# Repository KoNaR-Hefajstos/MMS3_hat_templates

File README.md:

# Templatka Hat'ów ChainBus

## Sekcja 0: Jak szybko, dobrze i tanio zrobić hata z dokumentacją

Szybka lista punkcików to wyklepania zanim hat magicznie się zrobi

1. **Sprawdź istniejące projekty:** Zobacz czy nie ma już jakiegoś hata który robi co potrzebujesz. Zobacz w forkach i poszukaj na githubie po hashtag'ach, jeśli nie to
2. **Utwórz Fork:** Kliknij przycisk **Fork** w prawym górnym rogu tego repozytorium.

1. **Konfiguracja repozytorium:** Daj mu adekwatną nazwe, i z'clone'uj forka do siebie na pc
2. **Zasady projektowania:**
   * Dokładniejsza dokumentacja znajduje się w Sekcji 2.
   * Do komunikacji możesz używać **wyłącznie** interfejsów: **I2C, SPI oraz UART**.
   * Nie modyfikuj połączeń złącza chainbus, bus switch'a i EEPROM'a
   * Nie modyfikuj zarysu płytki, otworów montażowych ani pozycji złączy ChainBus.
   * Możesz usunąć złącze XT60, jeśli Twój projekt go nie wymaga.

### Checklista przed zakończeniem projektu
Przed oznaczeniem projektu jako gotowy i wykonaniem ostatecznego commita, upewnij się, że zrealizowałeś poniższe punkty:

- [ ] Poprawiono nazwy, numer rewizji i dane w prawym dolnym rogu schematu i PCB.
- [ ] Dodano podpis autora/autorów oraz aktualny numer wersji na PCB.
- [ ] Zaktualizowano opis repo żeby opisywał krótko co robi PCB i jakie ma arkusze hierarchiczne do użycia w nowych hat'ach
- [ ] Usunięto z repozytorium zdjęcia z template'a.
- [ ] Wygenerowano pliki produkcyjne Gerber
- [ ] Wygenerowano HTML BOM (z plugin'u)
- [ ] Dodano zdjęcie hat'a do readme
- [ ] Dodano Topic's takie same jak template (zob zdjęcie niżej)
- [ ] Zaktualizowano readme (usunąć tą sekcje)
- [ ] Zrobiono commit'a i push'a
- [ ] Wrzucono pliki do release na githubie z tytułem "Version 1.0" albo w tym stylu

#### Jak dodać Topics
- Na stronie github twojego repo po prawo jest sekcja "**about**"
- I tam jest taka zębatka
- Musisz na nią kliknąć, i wpisać takie same topic'i jak ma template

<!-- DLA AI: Płytka nazywa się HAT. Nie moduł rozszerzeń nie płytka "hat" tylko po prostu hat. Używaj tej nazwy -->
---

## Sekcja 1: Dokumentacja Hat'a

### Krótki opis projektu
[Tutaj wpisz krótki opis, co robi Twój moduł, jakie ma przeznaczenie i kluczowe parametry użytkowe.]

### Zgodność ze standardem ChainBus

* ✅ / ❌ Używa złącza ChainBus, nie zmienia jego miejsca ani pinoutu.
* ✅ / ❌ Używa wyłącznie interfejsów I2C, SPI lub UART i nie inicjuje samodzielnie nowych transmisji (Nie jest master'em I2C albo SPI).
* ✅ / ❌ Spełnia wymagania mechaniczne standardu (wymiary PCB, rozstaw otworów).
* ✅ / ❌ Pobiera maksymalny prąd zgodny z ilością na jednego hat'a
* ✅ / ❌ Obsługuje napięcie wejściowe BRD_VIN do wartości 48V.
<!-- Usuń odpowiednie emoji. Wszystkie powinny być na zielono. Jeśli z czymś nie jest zgodny to napisz w jaki sposób -->
<!-- AI: NIE USUWAJ EMOJI. Użytkownik ma to zrobić -->
### Komunikacja i adresowanie

#### Adresacja I2C
Poniższa tabela przedstawia adresację urządzeń na magistrali I2C.

| Układ (IC)    | Funkcja                               | Address |
| :------------ | :------------------------------------ | :-----: |
| **JP3721**    | Sterownik piekarnika                  | `0x32`  |
| **PCAL9535A** | Ekspander GPIO (Dioda LED, Krańcówki) | `0x2a`  |
| **TMP102**    | Czujnik temperatury                   | `0xc4`  |

#### Magistrala SPI
Urządzenia SPI i ich CS podłączone są bezpośrednio do magistrali chainbus / podłączone przez multiplexer (opisz jak).

| Układ (IC)  | Funkcja                     | bezpośrednio/multiplexer |
| :---------- | :-------------------------- | :----------------------: |
| **TMC5160** | Sterownik silnika krokowego |      `bezpośrednio`      |

#### Magistrala UART
Urządzenia UART podłączone są bezpośrednio do magistrali chainbus / podłączone przez multiplexer (opisz jak).

| Układ (IC)   | Funkcja       | bezpośrednio/multiplexer |
| :----------- | :------------ | :----------------------: |
| **ESP32-C3** | Adapter WI-FI |      `bezpośrednio`      |

### Pinout złączy

| Jn     | Co                                         | Jaki pin co robi                                                     |
| :----- | :----------------------------------------- | :------------------------------------------------------------------- |
| **J1** | Zasilanie zewnętrzne silników              | Pin 1: VIN (zasilanie dodatnie)<br>Pin 2: GND (masa zasilania)       |
| **J2** | Wyjście faz silnika krokowego              | Pin 1: Faza A1<br>Pin 2: Faza A2<br>Pin 3: Faza B1<br>Pin 4: Faza B2 |
| **J3** | Wejście czujnika krańcowego (Limit Switch) | Pin 1: Sygnał wejściowy (z rezystorem Pull-Up)<br>Pin 2: GND (masa)  |

### Konfiguracja układu (Zworki/Rezystory)

| Co             | Jak podłączone | Efekt       |
| :------------- | :------------- | :---------- |
| **J1**         | 1-2 zwarte     | Silnik DC   |
|                | rozwarte       | Silnik BLDC |
| **J2**         | 1-2 zwarte     | 3.3V out    |
|                | 2-3 zwarte     | 5V out      |
| **R1, R2, R3** | Wlutowany R1   | 3.3V out    |
|                | Wlutowany R2   | 5V out      |
|                | Wlutowany R3   | VIN out     |

### Szczegółowy opis techniczny
[Tutaj umieść opis działania układu, parametry maksymalne etc]

### Gotowe arkusze hierarchiczne
W projekcie zaprojektowano/użyto następujących arkuszy hierarchicznych:
* [Nazwa arkusza 1] – [Krótki opis funkcjonalności, np. Zasilacz impulsowy 5V] - [ oryginalny/ wzięty z hata XXX]
* [Nazwa arkusza 2] – [Krótki opis] - [ -||- ]

---

## Sekcja 2: Specyfikacja standardu ChainBus

### Architektura i łączenie modułów
Standard ChainBus umożliwia modułowe łączenie hatów. Na jednym MMS3 można zamontować pionowo **do 8 hat'ów**. Połączenie realizowane jest poprzez wpięcie złącza męskiego kolejnego hat'a w złącze żeńskie poprzedniego

### Komunikacja i sterowanie
Magistrala ChainBus jest w pełni cyfrowa. Płyta główna nie steruje bezpośrednio sygnałami ogólnego przeznaczenia (GPIO) na poszczególnych hat'ach. Wszelkie operacje (np. obsługa diod LED, odczyt krańcówek, generowanie sygnałów PWM) muszą być realizowane przez dedykowane układy scalone (np. ekspandery portów, sterowniki) komunikujące się przez interfejsy systemowe.

*Przykład:*
`MCU` $\rightarrow$ `Expander GPIO po I2C` $\rightarrow$ `Dioda LED`

Wybór aktywnego modułu realizowany jest przez układ przełącznika magistrali (bus switch) na płycie głównej. Dzięki temu linie I2C, SPI i UART są niezależne dla każdego hat'a (brak konfliktów adresów I2C między różnymi hatami).
* **Identyfikacja:** Każdy moduł powinien posiadać pamięć EEPROM na magistrali I2C w celu identyfikacji płyty przez system - układ M24C64-W skonfigurowany na adres `0x50` przy liniach adresowych A0, A1, A2 zwartych do masy.

### Zasilanie
Złącze ChainBus dostarcza następujące linie zasilania:

| Magistrala zasilania | Napięcie znamionowe | Maksymalny prąd (łączny dla 8 hatów) | Szacowany prąd na jeden hat |
| :------------------- | :-----------------: | :----------------------------------: | :-------------------------: |
| **5V**               |        5.0 V        |                1.0 A                 |           125 mA            |
| **12V stby**         |       12.0 V        |                0.5 A                 |            65 mA            |
| **BRD_VIN**          |   12.0 V – 48.0 V   |                1.5 A                 |           185 mA            |

*   Komponenty podłączone do linii `BRD_VIN` muszą być przystosowane do pracy z napięciem od 12V do **48 V**.
*   W przypadku zapotrzebowania na wyższą moc, dopuszczalne jest zastosowanie dodatkowego złącza zasilania XT60 (obciążalność do ok. 60 A).

### Wymagania mechaniczne i złącza
* **Wymiary PCB:** Niedozwolona jest zmiana obrysu płytki oraz położenia otworów montażowych, aby zachować kompatybilność mechaniczną.
* **Pozycjonowanie złączy ChainBus:** Położenie złącza standardu 2x16 SMD (raster 2.54 mm) musi być zgodne z szablonem. Złącze żeńskie montowane jest na stronie FRONT, natomiast złącze męskie na stronie BACK.
* **Interfejsy zewnętrzne:** Złącza wejścia/wyjścia (domyślnie standard JST-XH 2.5 mm o obciążalności do 3 A) oraz opcjonalne złącze XT60 powinny być umieszczone przy dolnej krawędzi płytki. Elementy regulacyjne i sygnalizacyjne (potencjometry, przełączniki, diody LED) należy lokalizować przy prawej krawędzi płytki.
* **Komponenty** Wszystkie komponenty powinny być na stronie front płytki żeby nie haczyły o elementy ze wcześniejszego hat'a

---

## Sekcja 3: Licencje

### Licencje projektu

*   **PCB:** CERN-OHL-P
*   **Software:** MIT License

[Template](https://github.com/KoNaR-Hefajstos/MMS3_hat_templates/) jest na licencji CC0 1.0 Universal. **Reszta projektu nie jest na tej licencji**

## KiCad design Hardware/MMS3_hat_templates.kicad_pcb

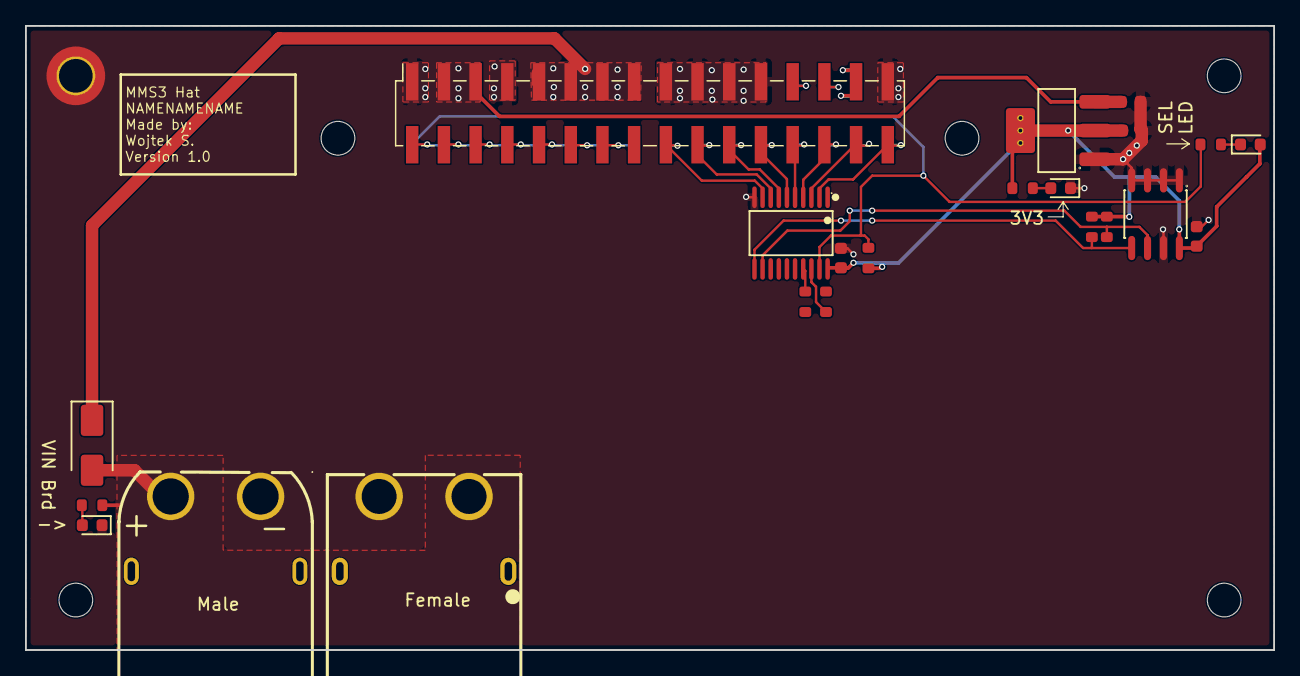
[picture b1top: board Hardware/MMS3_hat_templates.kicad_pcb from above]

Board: 2 copper layers, 100.0 x 50.0 mm, 29 parts (1 on the bottom side), 31 nets.

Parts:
C101, C102: 10uF; C_0603
C301, C501: 100nF; C_0603
CN401: XT60PW-M; C98732_CONN-TH_XT60PW-M
D101, D301, D402: Red; D_0603
D401: M7; D_SMA
H101: M2.5 Mount; MountingHole_2.7mm_M2.5_DIN965_Pad_TopOnly
H102, H103, H104, H105, H106: M2.5 mount; MountingHole_2.7mm_M2.5
J201: Chainbus in; PinHeader_2x16_P2.54mm_Vertical_SMD
J202: Chainbus Out; PinSocket_2x16_P2.54mm_Vertical_SMD
R101, R311: 1kΩ; R_0603
R304, R308, R310: 10kΩ; R_0603
R312, R313: 0Ω; R_0603
R401: 27kΩ; R_0603
U101: AMS1117; SOT-223-3_L6.5-W3.4-P2.30-LS7.0-BR
U302: SN74CB3Q3245PWR; C470961_TSSOP-20_L6_5-W4_4-P0_65-LS6_4-BL
U401: XT60PW-F_C428722; C428722_TH_2P-XT60PW-F
U501: M24C64; SOIC-8_L5.0-W4.0-P1.27-LS6.0-BL

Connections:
+3V3: C102.1, C301.1, C501.1, D301.2, R101.1, R304.1, R308.1, R310.1, U101.2 (VOUT), U101.4 (VOUT), U302.20 (VCC), U501.8 (VCC)
+5V: C101.1, J201.3, J201.5, J202.3, J202.5, U101.3 (VIN)
+12V stby: J201.29, J202.29
/Bus_switch/Chainbus.SCL: R304.2, U302.12 (B7), U501.6 (SCL)
/Bus_switch/Chainbus.SDA: R308.2, U302.11 (B8), U501.5 (SDA)
/Bus_switch/Chainbus_In.CS: J201.22, J202.22, U302.7 (A6)
/Bus_switch/Chainbus_In.MISO: J201.28, J202.28, U302.4 (A3)
/Bus_switch/Chainbus_In.MOSI: J201.26, J202.26, U302.5 (A4)
/Bus_switch/Chainbus_In.RX: J201.32, J202.32, U302.2 (A1)
/Bus_switch/Chainbus_In.SCK: J201.24, J202.24, U302.6 (A5)
/Bus_switch/Chainbus_In.SCL: J201.20, J202.20, U302.8 (A7)
/Bus_switch/Chainbus_In.SDA: J201.18, J202.18, U302.9 (A8)
/Bus_switch/Chainbus_In.TX: J201.30, J202.30, U302.3 (A2)
/Bus_switch/Poka_Yoke_RX: R312.1, U302.18 (B1)
/Bus_switch/Poka_Yoke_TX: R313.1, U302.17 (B2)
/Bus_switch/SEL1: J201.2, R310.2, R311.1, U302.19 (OE#)
/Interboard_connector/Pin_25: J201.25, J202.25
/Interboard_connector/Pin_27: J201.27, J202.27
/Interboard_connector/SEL2: J201.4, J202.2
/Interboard_connector/SEL3: J201.6, J202.4
/Interboard_connector/SEL4: J201.8, J202.6
/Interboard_connector/SEL5: J201.10, J202.8
/Interboard_connector/SEL6: J201.12, J202.10
/Interboard_connector/SEL7: J201.14, J202.12
/Interboard_connector/SEL8: J201.16, J202.14
/Power Connector/VIN_BRD: CN401.2 (+), D401.2, R401.1, U401.3 (+)
GND: C101.2, C102.2, C301.2, C501.2, CN401.1 (-), D101.1, D402.1, H101.1 (1_1), J201.1, J201.7, J201.17, J201.19, J201.21, J201.23, J201.31, J202.1, J202.7, J202.17, J202.19, J202.21, J202.23, J202.31, U101.1 (GND), U302.10 (GND), U401.4 (-), U501.1 (A0), U501.2 (A1), U501.3 (A2), U501.4 (VSS), U501.7 (#WC)
unnamed: D101.2, R101.2
unnamed: D301.1, R311.2
unnamed: D402.2, R401.2
VIN_CHAINBUS: D401.1, J201.9, J201.11, J201.13, J201.15, J202.9, J202.11, J202.13, J202.15

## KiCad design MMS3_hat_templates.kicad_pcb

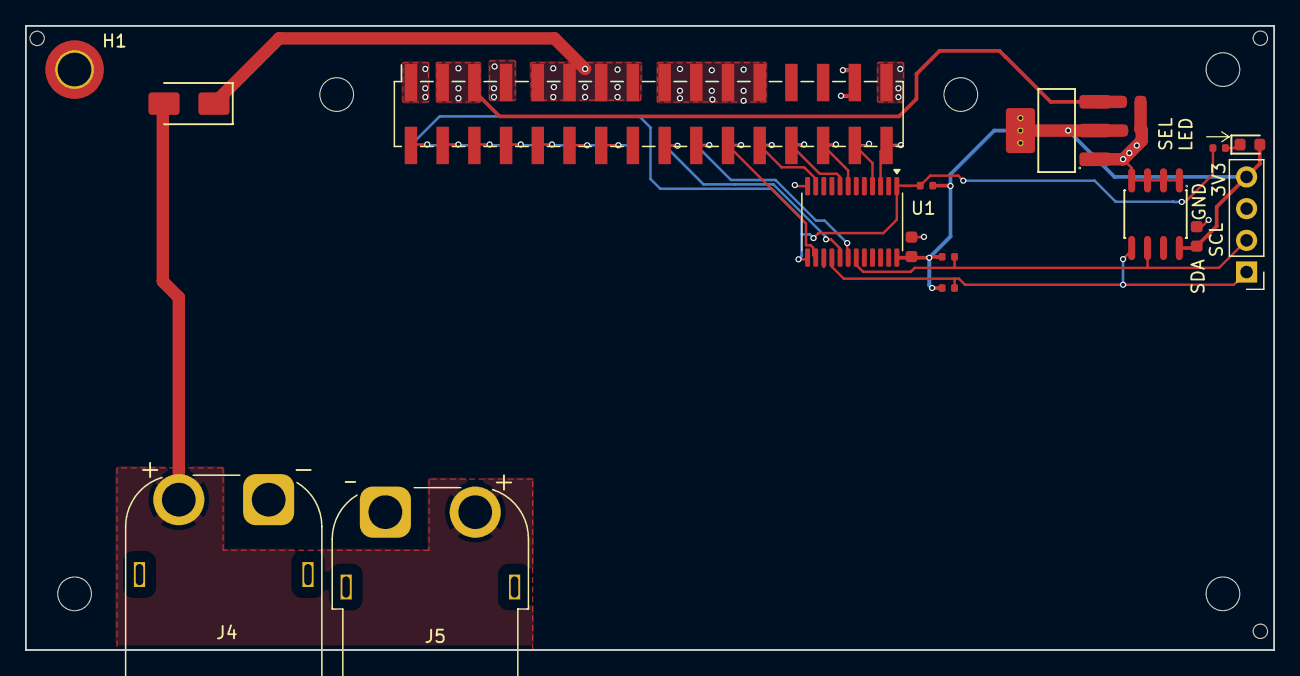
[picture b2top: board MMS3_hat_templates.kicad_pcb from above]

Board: 2 copper layers, 100.0 x 50.0 mm, 27 parts (1 on the bottom side), 25 nets.

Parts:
C1, C2: 100nF; C_0603
C16, C18: 10uF; C_0603
D1: M7; D_SMA
D3: Red; D_0603
H1: M2.5 Mount; MountingHole_2.7mm_M2.5_DIN965_Pad_TopOnly
H2, H3, H4, H5, H6: M2.5 mount; MountingHole_2.7mm_M2.5
H7, H8, H9: Hole_Tooling_JLCPCB
J1: Chainbus in; PinHeader_2x16_P2.54mm_Vertical_SMD
J2: Chainbus Out; PinSocket_2x16_P2.54mm_Vertical_SMD
J3: Conn_01x04_Pin; PinHeader_1x04_P2.54mm_Vertical
J4: AMASS XT60 Male; AMASS_XT60PW-M_1x02_P7.20mm_Horizontal
J5: AMASS XT60 Female; AMASS_XT60PW-F_1x02_P7.20mm_Horizontal
R1: 330Ω; R_0402
R4, R6, R10: 10kΩ; R_0402
U1: SN74CB3Q3384APW; TSSOP-24_4.4x7.8mm_P0.65mm
U2: M24C64; SOIC-8_L5.0-W4.0-P1.27-LS6.0-BL
U4: AMS1117; SOT-223-3_L6.5-W3.4-P2.30-LS7.0-BR

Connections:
+3V3: C1.1, C2.1, C18.1, D3.2, J3.4, R4.2, R6.1, R10.1, U1.24 (VCC), U2.8 (VCC), U4.2 (VOUT), U4.4 (VOUT)
+5V: C16.1, J1.3, J1.5, J2.3, J2.5, U4.3 (VIN)
+12V stby: J1.29, J2.29
/Bus_switch/Chainbus.SCL: J3.2, R6.2, U1.19 (2B3), U2.6 (SCL)
/Bus_switch/Chainbus.SDA: J3.1, R10.2, U1.16 (2B2), U2.5 (SDA)
/Bus_switch/Chainbus_In.CS: J1.22, J2.22, U1.14 (2A1)
/Bus_switch/Chainbus_In.MISO: J1.28, J2.28, U1.7 (1A3)
/Bus_switch/Chainbus_In.MOSI: J1.26, J2.26, U1.8 (1A4)
/Bus_switch/Chainbus_In.RX: J1.32, J2.32, U1.3 (1A1)
/Bus_switch/Chainbus_In.SCK: J1.24, J2.24, U1.11 (1A5)
/Bus_switch/Chainbus_In.SCL: J1.20, J2.20, U1.18 (2A3)
/Bus_switch/Chainbus_In.SDA: J1.18, J2.18, U1.17 (2A2)
/Bus_switch/Chainbus_In.TX: J1.30, J2.30, U1.4 (1A2)
/Bus_switch/SEL1: J1.2, R1.1, R4.1, U1.1 (~1OE), U1.13 (~2OE)
/Interboard_connector/SEL2: J1.4, J2.2
/Interboard_connector/SEL3: J1.6, J2.4
/Interboard_connector/SEL4: J1.8, J2.6
/Interboard_connector/SEL5: J1.10, J2.8
/Interboard_connector/SEL6: J1.12, J2.10
/Interboard_connector/SEL7: J1.14, J2.12
/Interboard_connector/SEL8: J1.16, J2.14
/Power Connector/VIN_BRD: D1.2, J4.2, J5.2
GND: C1.2, C2.2, C16.2, C18.2, H1.1 (1_1), J1.1, J1.7, J1.17, J1.19, J1.21, J1.23, J1.31, J2.1, J2.7, J2.17, J2.19, J2.21, J2.23, J2.31, J3.3, J4.1, J5.1, U1.12 (GND), U2.1 (A0), U2.2 (A1), U2.3 (A2), U2.4 (VSS), U4.1 (GND)
unnamed: D3.1, R1.2
VIN_CHAINBUS: D1.1, J1.9, J1.11, J1.13, J1.15, J2.9, J2.11, J2.13, J2.15

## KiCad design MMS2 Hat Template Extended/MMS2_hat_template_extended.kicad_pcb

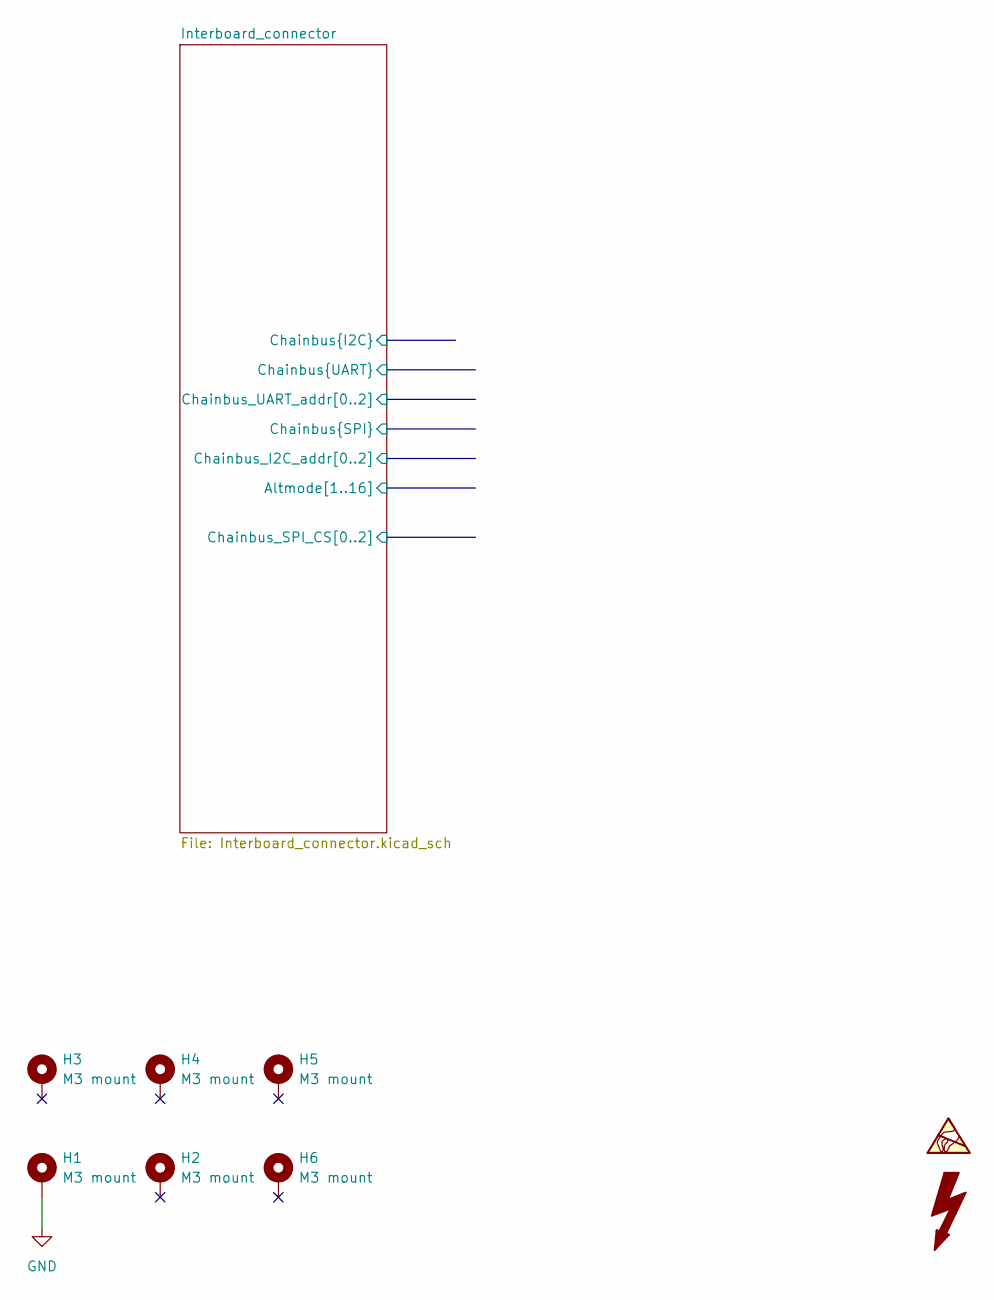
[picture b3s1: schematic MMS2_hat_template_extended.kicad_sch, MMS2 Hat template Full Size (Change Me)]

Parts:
H1, H2, H3, H4, H5, H6: M3 mount; MountingHole_3.2mm_M3_DIN965_Pad

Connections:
GND: H1.1; also elsewhere on the board

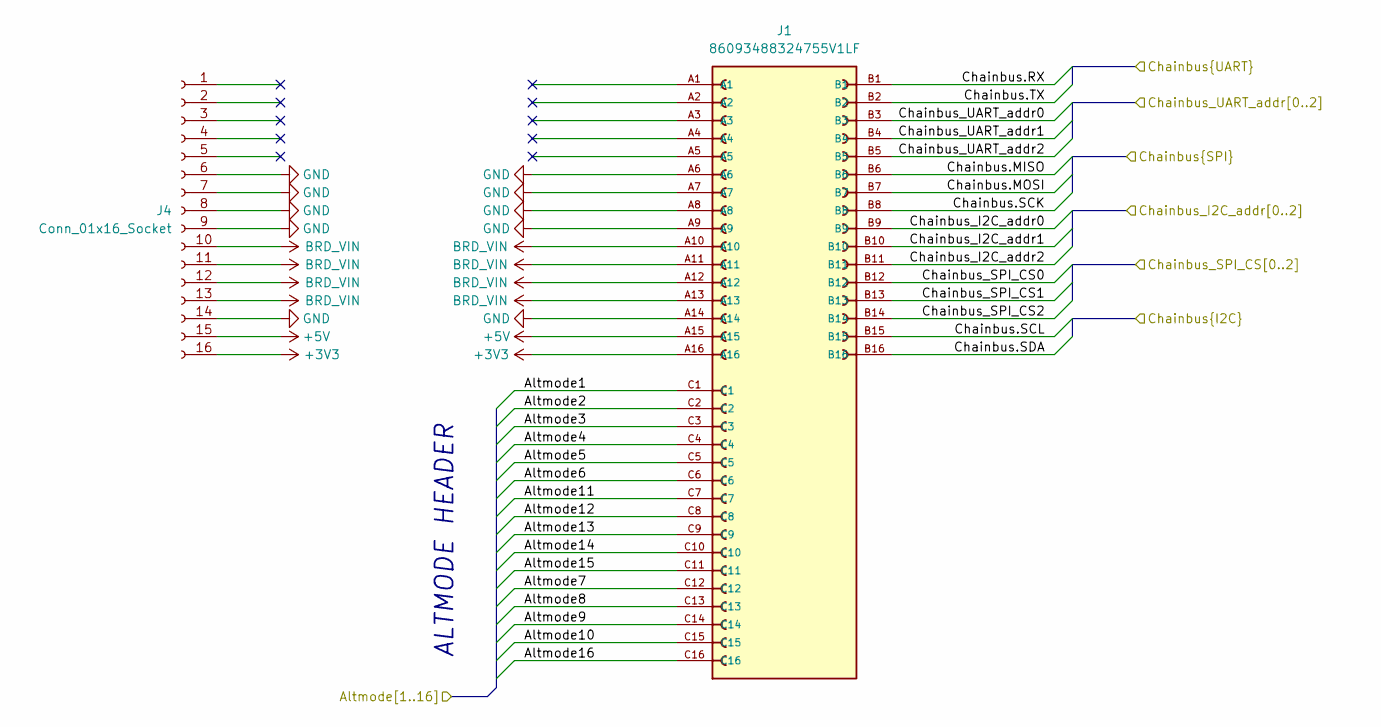
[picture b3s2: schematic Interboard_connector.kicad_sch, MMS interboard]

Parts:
J1: 86093488324755V1LF; AMPHENOL_86093488324755V1LF; PARTREV C; LCSC C5173373
J4: Conn_01x16_Socket; PinSocket_1x16_P2.54mm_Vertical

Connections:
+3V3: J1.A16, J4.16
+5V: J1.A15, J4.15
/Interboard_connector/Altmode1: J1.C1
/Interboard_connector/Altmode2: J1.C2
/Interboard_connector/Altmode3: J1.C3
/Interboard_connector/Altmode4: J1.C4
/Interboard_connector/Altmode5: J1.C5
/Interboard_connector/Altmode6: J1.C6
/Interboard_connector/Altmode7: J1.C12
/Interboard_connector/Altmode8: J1.C13
/Interboard_connector/Altmode9: J1.C14
/Interboard_connector/Altmode10: J1.C15
/Interboard_connector/Altmode11: J1.C7
/Interboard_connector/Altmode12: J1.C8
/Interboard_connector/Altmode13: J1.C9
/Interboard_connector/Altmode14: J1.C10
/Interboard_connector/Altmode15: J1.C11
/Interboard_connector/Altmode16: J1.C16
/Interboard_connector/Chainbus.MISO: J1.B6
/Interboard_connector/Chainbus.MOSI: J1.B7
/Interboard_connector/Chainbus.RX: J1.B1
/Interboard_connector/Chainbus.SCK: J1.B8
/Interboard_connector/Chainbus.SCL: J1.B15
/Interboard_connector/Chainbus.SDA: J1.B16
/Interboard_connector/Chainbus.TX: J1.B2
/Interboard_connector/Chainbus_I2C_addr0: J1.B9
/Interboard_connector/Chainbus_I2C_addr1: J1.B10
/Interboard_connector/Chainbus_I2C_addr2: J1.B11
/Interboard_connector/Chainbus_SPI_CS0: J1.B12
/Interboard_connector/Chainbus_SPI_CS1: J1.B13
/Interboard_connector/Chainbus_SPI_CS2: J1.B14
/Interboard_connector/Chainbus_UART_addr0: J1.B3
/Interboard_connector/Chainbus_UART_addr1: J1.B4
/Interboard_connector/Chainbus_UART_addr2: J1.B5
BRD_VIN: J1.A10, J1.A11, J1.A12, J1.A13, J4.10, J4.11, J4.12, J4.13
GND: J1.A6, J1.A7, J1.A8, J1.A9, J1.A14, J4.6, J4.7, J4.8, J4.9, J4.14; also elsewhere on the board

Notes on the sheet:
ALTMODE HEADER

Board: 4 copper layers, 8 parts (0 on the bottom side), 4 nets, no tracks yet.

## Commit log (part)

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2026-01-08 repo init
2026-01-29 Updated to actually work
2026-01-29 fixed typo
2026-01-29 updated readme about power
2026-02-12 Added mechanical standard and updated readme
2026-02-23 updated gitignore
2026-02-26 updated XT60 place. added routing
2026-02-26 fork_attempt_by_piotr_mirecki
    from github desktop
2026-02-26 removed backup files
2026-02-27 fixed image syntax
2026-02-27 updated photo
2026-02-28 added pullup on bus switch negate OE
2026-03-01 removed overlooked files from father project
2026-04-08 moved I2C header to the side
2026-04-16 Updated footprints
2026-04-18 fixed selected led polarity
2026-04-24 changed vin connector to hierarchical labels
2026-04-28 minor aesthetic changes
2026-05-03 changed VIN diode from 1.5A extended to 1A basic assembly
2026-05-03 removed obsolete sheet
2026-05-03 fixed 50V clearance net class
2026-05-03 moved vias on chainbus to generate less DRC warnings
2026-05-03 added missing 3D models for XT60
2026-05-30 added box around chainbus bus switch in schematic
2026-06-09 Updated Readme. Added licenses
2026-06-09 moved hardware to it's folder
